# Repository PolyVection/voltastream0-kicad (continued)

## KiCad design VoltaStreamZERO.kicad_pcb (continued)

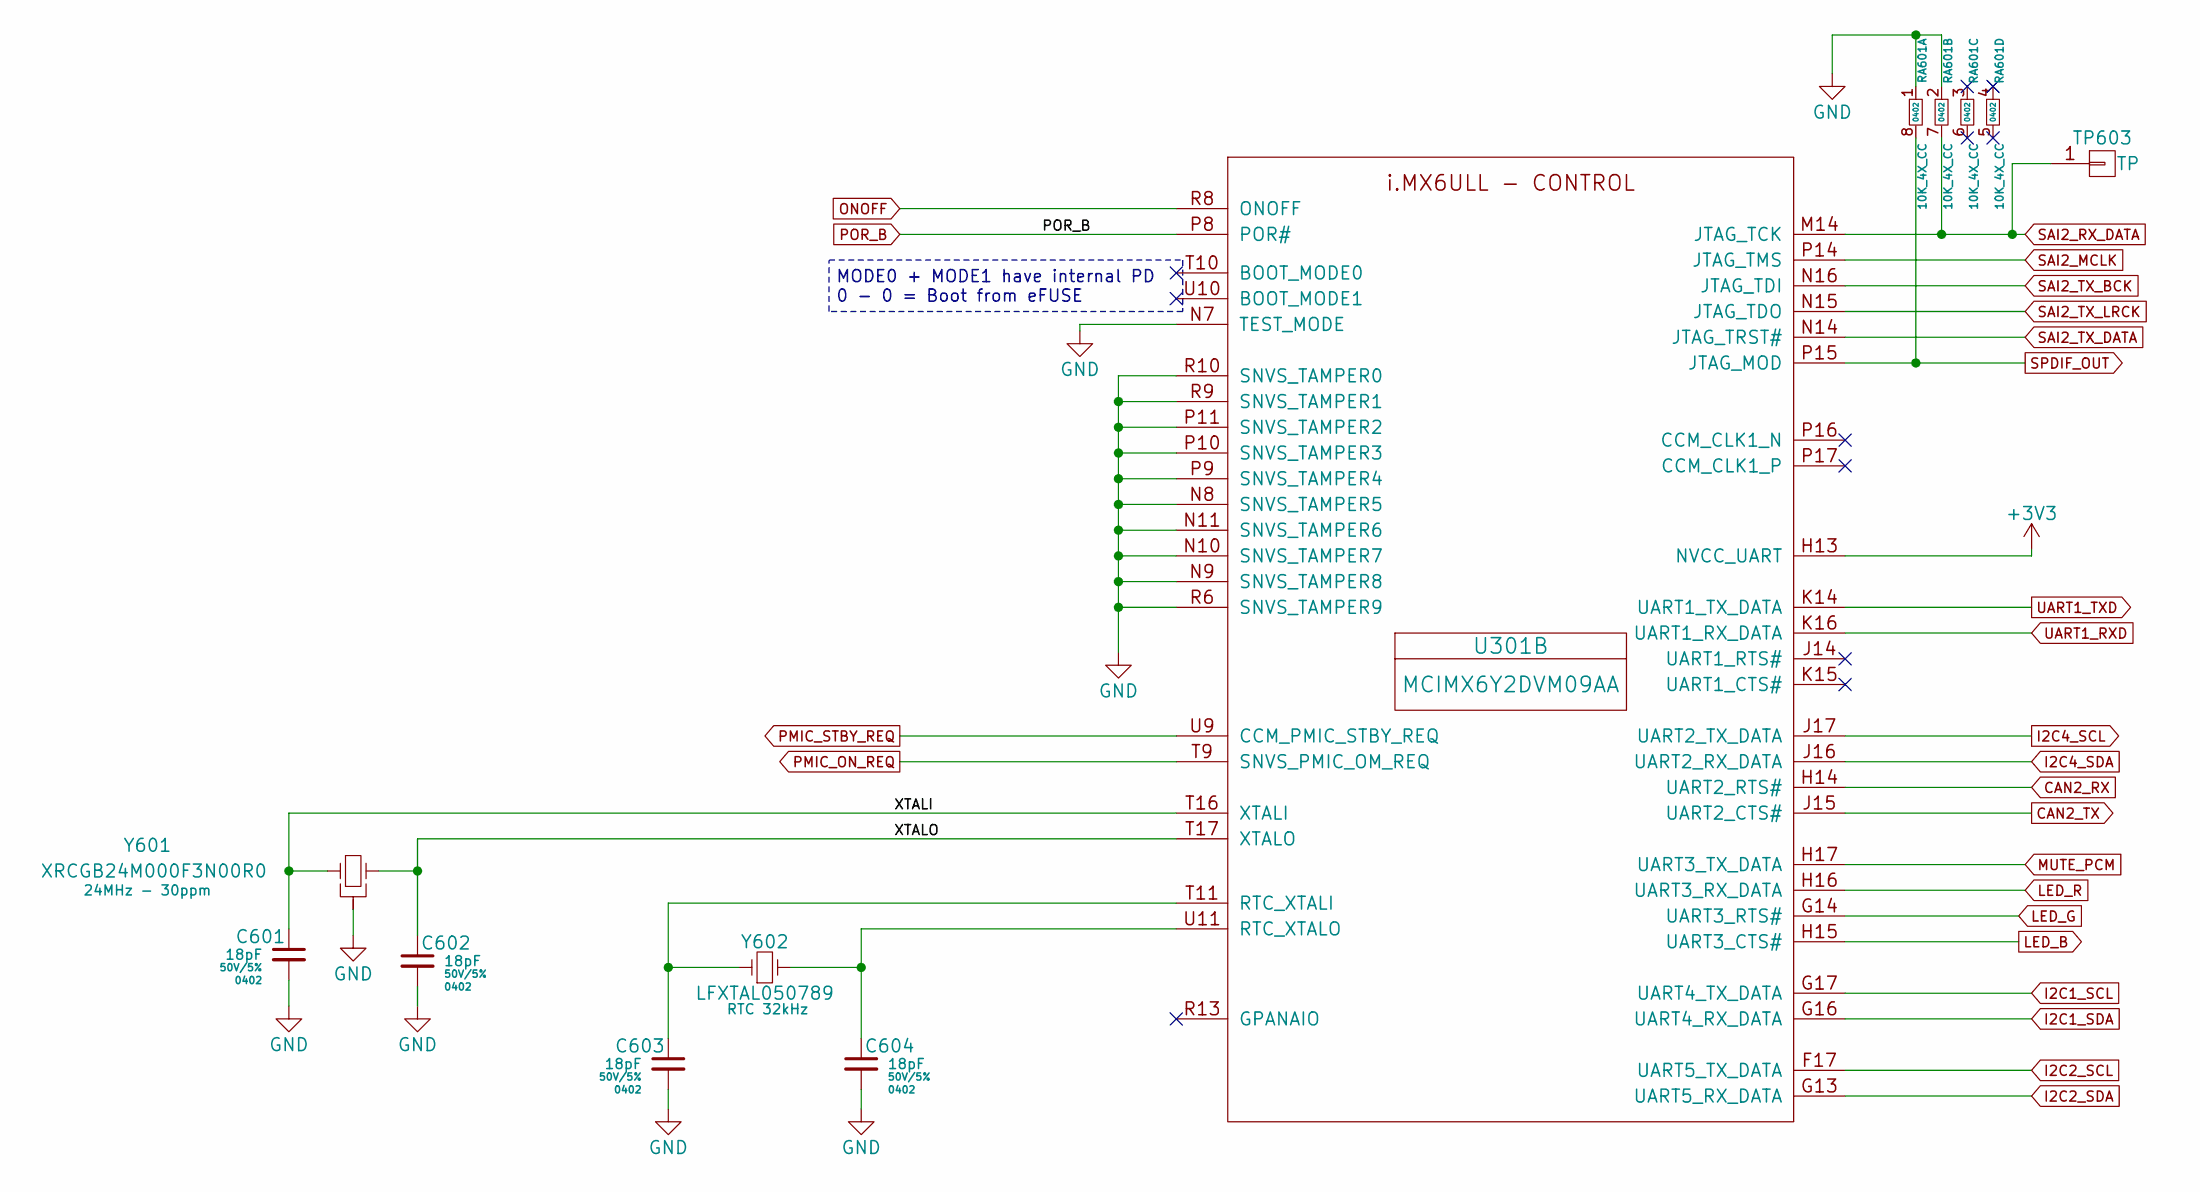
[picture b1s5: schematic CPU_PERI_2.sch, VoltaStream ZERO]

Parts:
C601, C602, C603, C604: 18pF; 0402; Rating 50V/5%; Rating2 C0G; Part GRM1555C1H180JA01D
RA601: 10K_4X_CC; R_Array_OPT_4x0402; Rating 10K, 5%; Rating2 Concave Array 4x; Part EXB-N8V103JX
TP603: TP; TP_10; Rating NoMask; Part TestPoint
U301: MCIMX6Y2DVM09AA; BGA_14x14; Rating 1x 900 MHz, 32 bit; Part MCIMX6Y2DVM09AA
Y601: XRCGB24M000F3N00R0; OSZ_2x1.6; Rating 24MHz - 30ppm; Rating2 6pF - 2x1.6mm; Part XRCGB24M000F3N00R0
Y602: LFXTAL050789; OSZ_2x1.2; Rating RTC 32kHz; Part LFXTAL050789Reel

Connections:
+3V3: U301.H13 (NVCC_UART); also elsewhere on the board
/CPU_PERI_2/XTALI: C601.1, U301.T16 (XTALI), Y601.1
/CPU_PERI_2/XTALO: C602.1, U301.T17 (XTALO), Y601.2
CAN2_RX: U301.H14 (UART2_RTS#)
CAN2_TX: U301.J15 (UART2_CTS#)
GND: C601.2, C602.2, C603.2, C604.2, RA601.1, RA601.2 (P1), U301.N7 (TEST_MODE), U301.N8 (SNVS_TAMPER5), U301.N9 (SNVS_TAMPER8), U301.N10 (SNVS_TAMPER7), U301.N11 (SNVS_TAMPER6), U301.P9 (SNVS_TAMPER4), U301.P10 (SNVS_TAMPER3), U301.P11 (SNVS_TAMPER2), U301.R6 (SNVS_TAMPER9), U301.R9 (SNVS_TAMPER1), U301.R10 (SNVS_TAMPER0), Y601.G; also elsewhere on the board
I2C1_SCL: U301.G17 (UART4_TX_DATA); also elsewhere on the board
I2C1_SDA: U301.G16 (UART4_RX_DATA); also elsewhere on the board
I2C2_SCL: U301.F17 (UART5_TX_DATA)
I2C2_SDA: U301.G13 (UART5_RX_DATA)
I2C4_SCL: U301.J17 (UART2_TX_DATA); also elsewhere on the board
I2C4_SDA: U301.J16 (UART2_RX_DATA); also elsewhere on the board
LED_B: U301.H15 (UART3_CTS#); also elsewhere on the board
LED_G: U301.G14 (UART3_RTS#); also elsewhere on the board
LED_R: U301.H16 (UART3_RX_DATA); also elsewhere on the board
MUTE_PCM: U301.H17 (UART3_TX_DATA); also elsewhere on the board
unnamed: C603.1, U301.T11 (RTC_XTALI), Y602.1
unnamed: C604.1, U301.U11 (RTC_XTALO), Y602.2
ONOFF: U301.R8 (ONOFF); also elsewhere on the board
PMIC_ON_REQ: U301.T9 (SNVS_PMIC_OM_REQ); also elsewhere on the board
PMIC_STBY_REQ: U301.U9 (CCM_PMIC_STBY_REQ)
POR_B: U301.P8 (POR#); also elsewhere on the board
SAI2_MCLK: U301.P14 (JTAG_TMS); also elsewhere on the board
SAI2_RX_DATA: RA601.7 (R1), TP603.1, U301.M14 (JTAG_TCK)
SAI2_TX_BCK: U301.N16 (JTAG_TDI); also elsewhere on the board
SAI2_TX_DATA: U301.N14 (JTAG_TRST#); also elsewhere on the board
SAI2_TX_LRCK: U301.N15 (JTAG_TDO); also elsewhere on the board
SPDIF_OUT: RA601.8 (R1), U301.P15 (JTAG_MOD); also elsewhere on the board
UART1_RXD: U301.K16 (UART1_RX_DATA); also elsewhere on the board
UART1_TXD: U301.K14 (UART1_TX_DATA); also elsewhere on the board

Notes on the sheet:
MODE0 + MODE1 have internal PD 0 - 0 = Boot from eFUSE

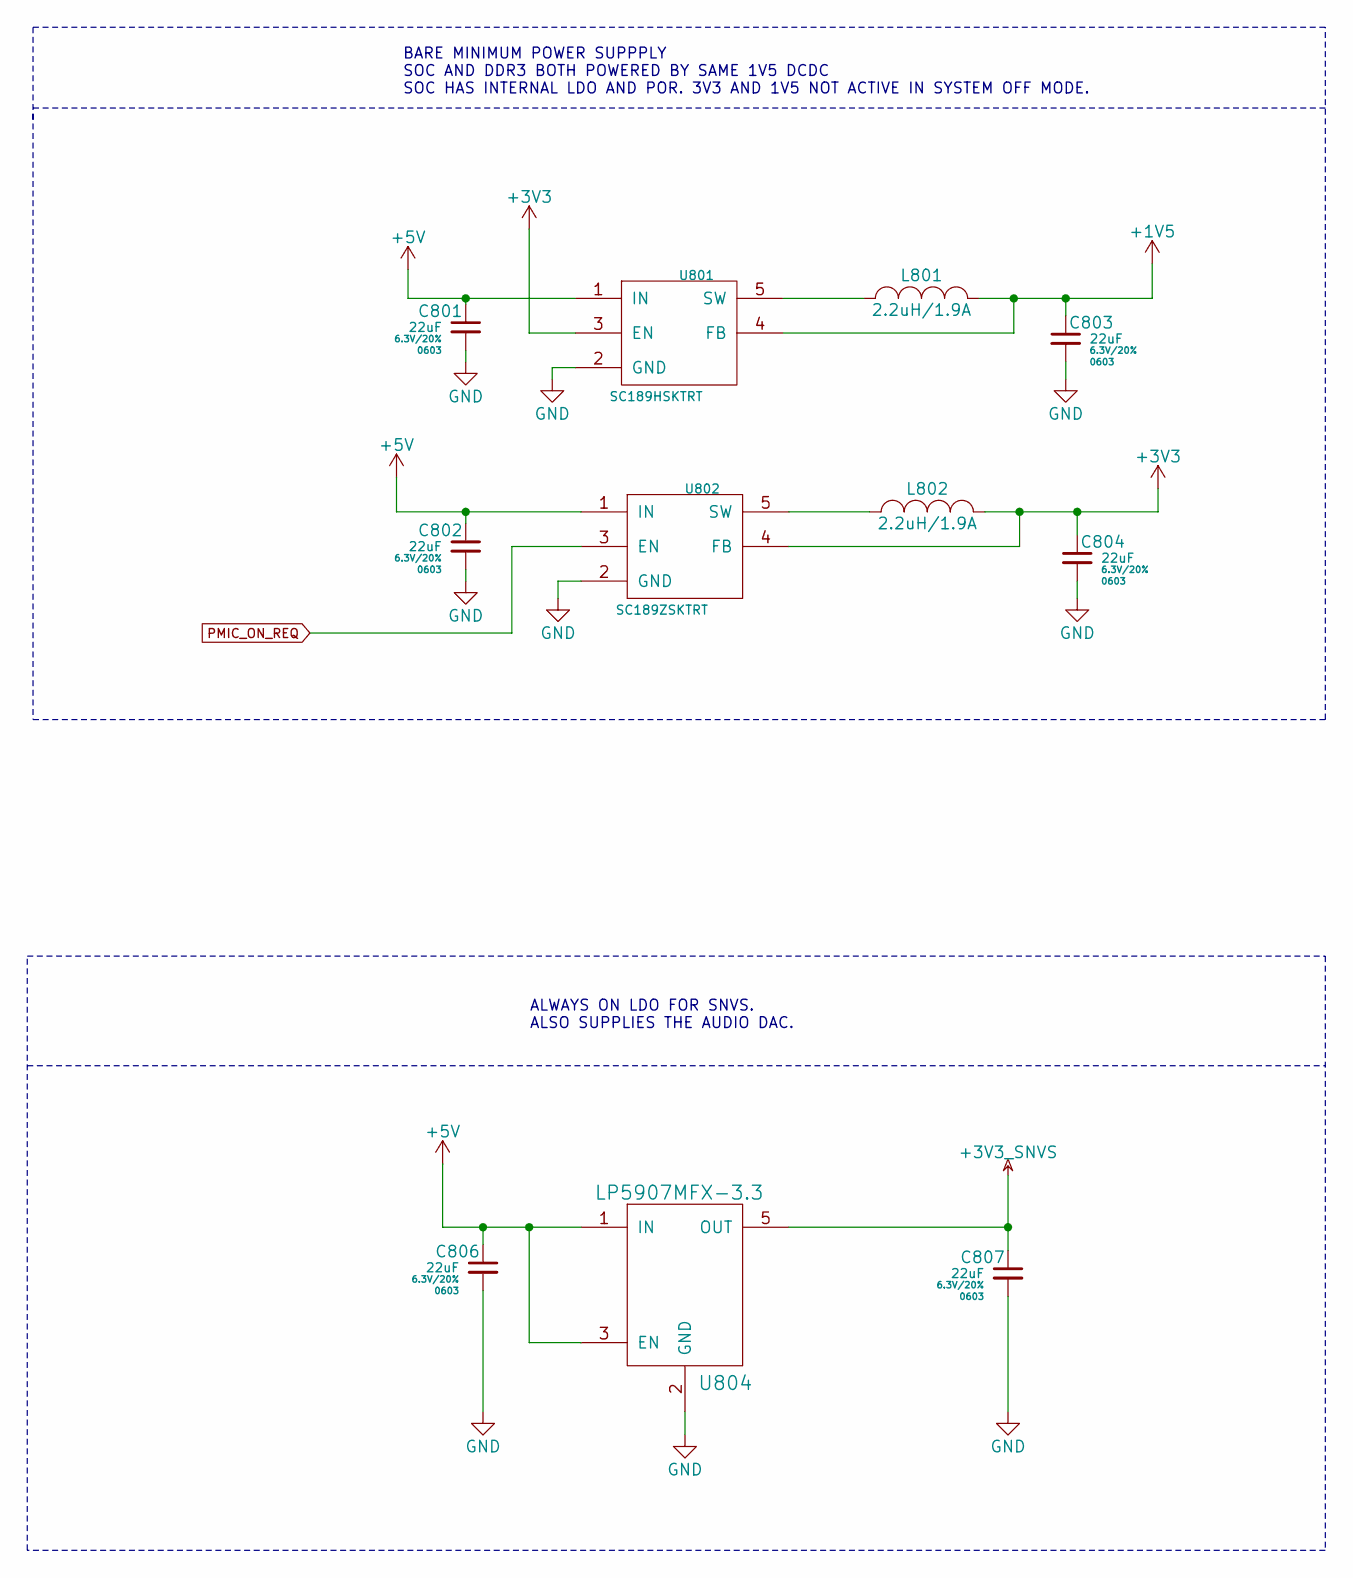
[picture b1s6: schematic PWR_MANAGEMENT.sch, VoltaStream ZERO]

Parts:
C801, C802, C803, C804, C806, C807: 22uF; 0603; Rating 6.3V/20%; Rating2 X5R; Part GRM188R60J226ME0D
L801, L802: 2.2uH/1.9A; MAMK2520T2R2M; Rating 2.2uH / 1.9A; Part MAMK2520T2R2M
U801: SC189HSKTRT; SOT-23-5; Rating 1V5 1.5A 2.5MHz; Rating2 STEP DOWN; Part SC189HSKTRT
U802: SC189ZSKTRT; SOT-23-5; Rating 3V3 1.5A 2.5MHz; Rating2 STEP DOWN; Part SC189ZSKTRT
U804: LP5907MFX-3.3; SOT-23-5; Rating 3V3 LDO LOW-NOISE; Rating2 250mA; Part LP5907MFX-3.3

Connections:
+1V5: C803.1, L801.2, U801.4 (FB); also elsewhere on the board
+3V3: C804.1, L802.2, U801.3 (EN), U802.4 (FB); also elsewhere on the board
+3V3_SNVS: C807.1, U804.5 (OUT); also elsewhere on the board
+5V: C801.1, C802.1, C806.1, U801.1 (IN), U802.1 (IN), U804.1 (IN), U804.3 (EN); also elsewhere on the board
GND: C801.2, C802.2, C803.2, C804.2, C806.2, C807.2, U801.2 (GND), U802.2 (GND), U804.2 (GND); also elsewhere on the board
unnamed: L801.1, U801.5 (SW)
unnamed: L802.1, U802.5 (SW)
PMIC_ON_REQ: U802.3 (EN); also elsewhere on the board

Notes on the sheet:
BARE MINIMUM POWER SUPPPLY SOC AND DDR3 BOTH POWERED BY SAME 1V5 DCDC SOC HAS INTERNAL LDO AND POR. 3V3 AND 1V5 NOT ACTIVE IN SYSTEM OFF MODE.
ALWAYS ON LDO FOR SNVS. ALSO SUPPLIES THE AUDIO DAC.

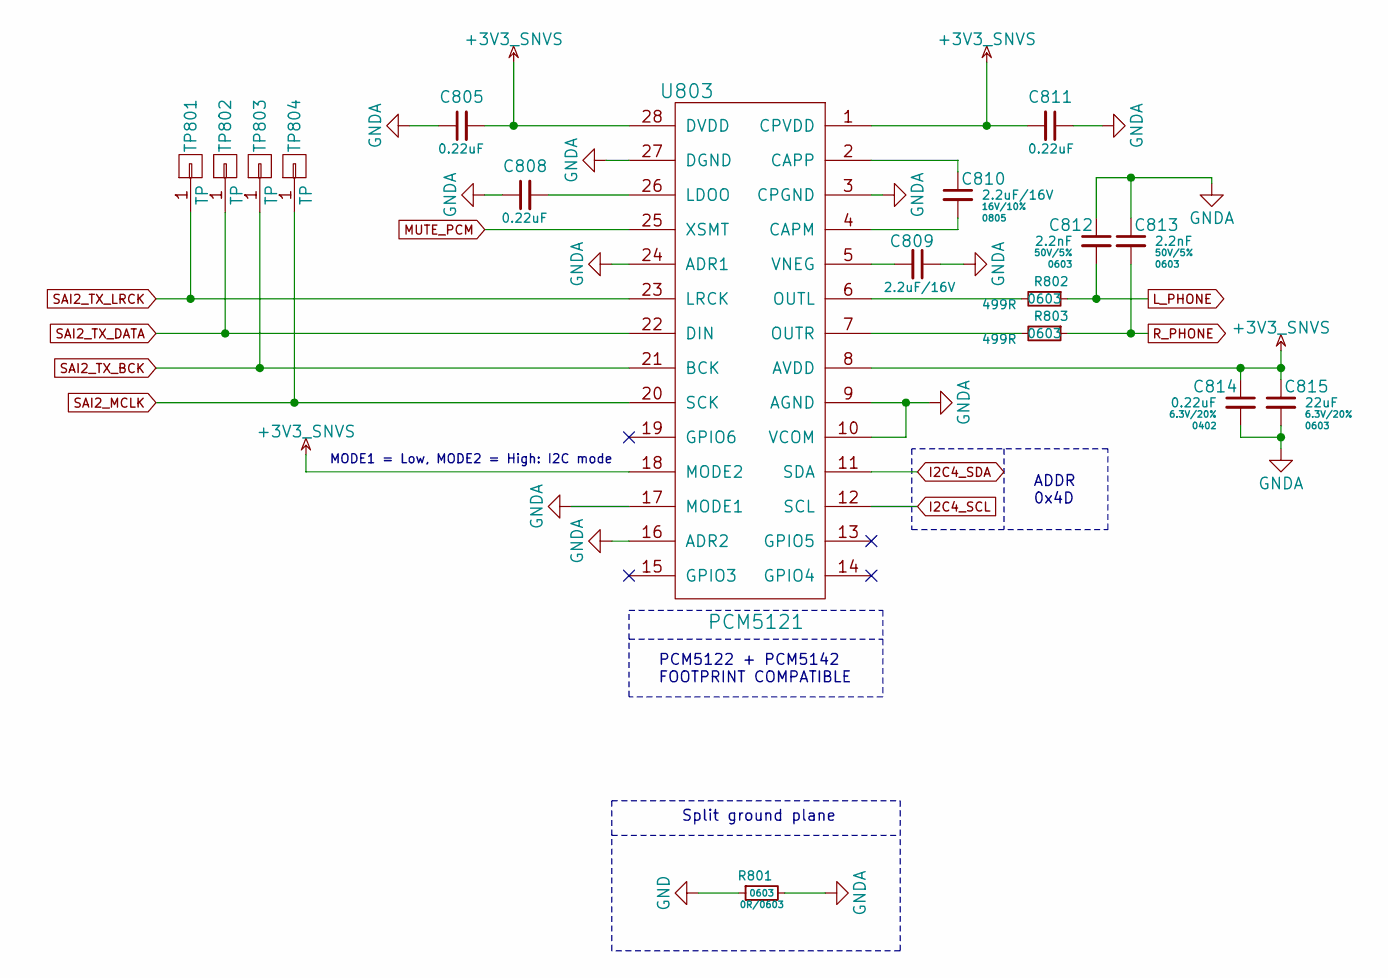
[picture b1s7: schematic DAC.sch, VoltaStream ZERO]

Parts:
C805, C808, C811, C814: 0.22uF; 0402; Rating 6.3V/20%; Rating2 X5R; Part GRM155R60J224KE01D
C809, C810: 2.2uF/16V; 0805; Rating 16V/10%; Rating2 X7R; Part GRM21BR71C225KA12L
C812, C813: 2.2nF; 0603; Rating 50V/5%; Rating2 X7R; Part GRM188R71H222JA01D
C815: 22uF; 0603; Rating 6.3V/20%; Rating2 X5R; Part GRM188R60J226ME0D
R801: 0R/0603; 0603; Rating 1% / Thick Film; Part RC0603FR-070RL
R802, R803: 499R; 0603; Rating 1% / Thick Film; Part RC0603FR-07499RL
TP801, TP802, TP803, TP804: TP; TP_10; Rating NoMask; Part TestPoint
U803: PCM5121; TSSOP-28_4.4x9.7mm_Pitch0.65mm; Rating 106dB DAC BurrBrown; Rating2 HW VOLUME; Part PCM5121PWR

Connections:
+3V3_SNVS: C805.2, C811.2, C814.1, C815.1, U803.1 (CPVDD), U803.8 (AVDD), U803.18 (MODE2), U803.28 (DVDD); also elsewhere on the board
GND: R801.1; also elsewhere on the board
GNDA: C805.1, C808.1, C809.1, C811.1, C812.1, C813.1, C814.2, C815.2, R801.2, U803.3 (CPGND), U803.9 (AGND), U803.10 (VCOM), U803.16 (ADR2), U803.17 (MODE1), U803.24 (ADR1), U803.27 (DGND); also elsewhere on the board
I2C4_SCL: U803.12 (SCL); also elsewhere on the board
I2C4_SDA: U803.11 (SDA); also elsewhere on the board
L_PHONE: C812.2, R802.1; also elsewhere on the board
MUTE_PCM: U803.25 (XSMT); also elsewhere on the board
unnamed: C808.2, U803.26 (LDOO)
unnamed: C809.2, U803.5 (VNEG)
unnamed: C810.1, U803.2 (CAPP)
unnamed: C810.2, U803.4 (CAPM)
unnamed: R802.2, U803.6 (OUTL)
unnamed: R803.2, U803.7 (OUTR)
R_PHONE: C813.2, R803.1; also elsewhere on the board
SAI2_MCLK: TP804.1, U803.20 (SCK); also elsewhere on the board
SAI2_TX_BCK: TP803.1, U803.21 (BCK); also elsewhere on the board
SAI2_TX_DATA: TP802.1, U803.22 (DIN); also elsewhere on the board
SAI2_TX_LRCK: TP801.1, U803.23 (LRCK); also elsewhere on the board

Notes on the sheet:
MODE1 = Low, MODE2 = High: I2C mode
Split ground plane
ADDR 0x4D
PCM5122 + PCM5142 FOOTPRINT COMPATIBLE

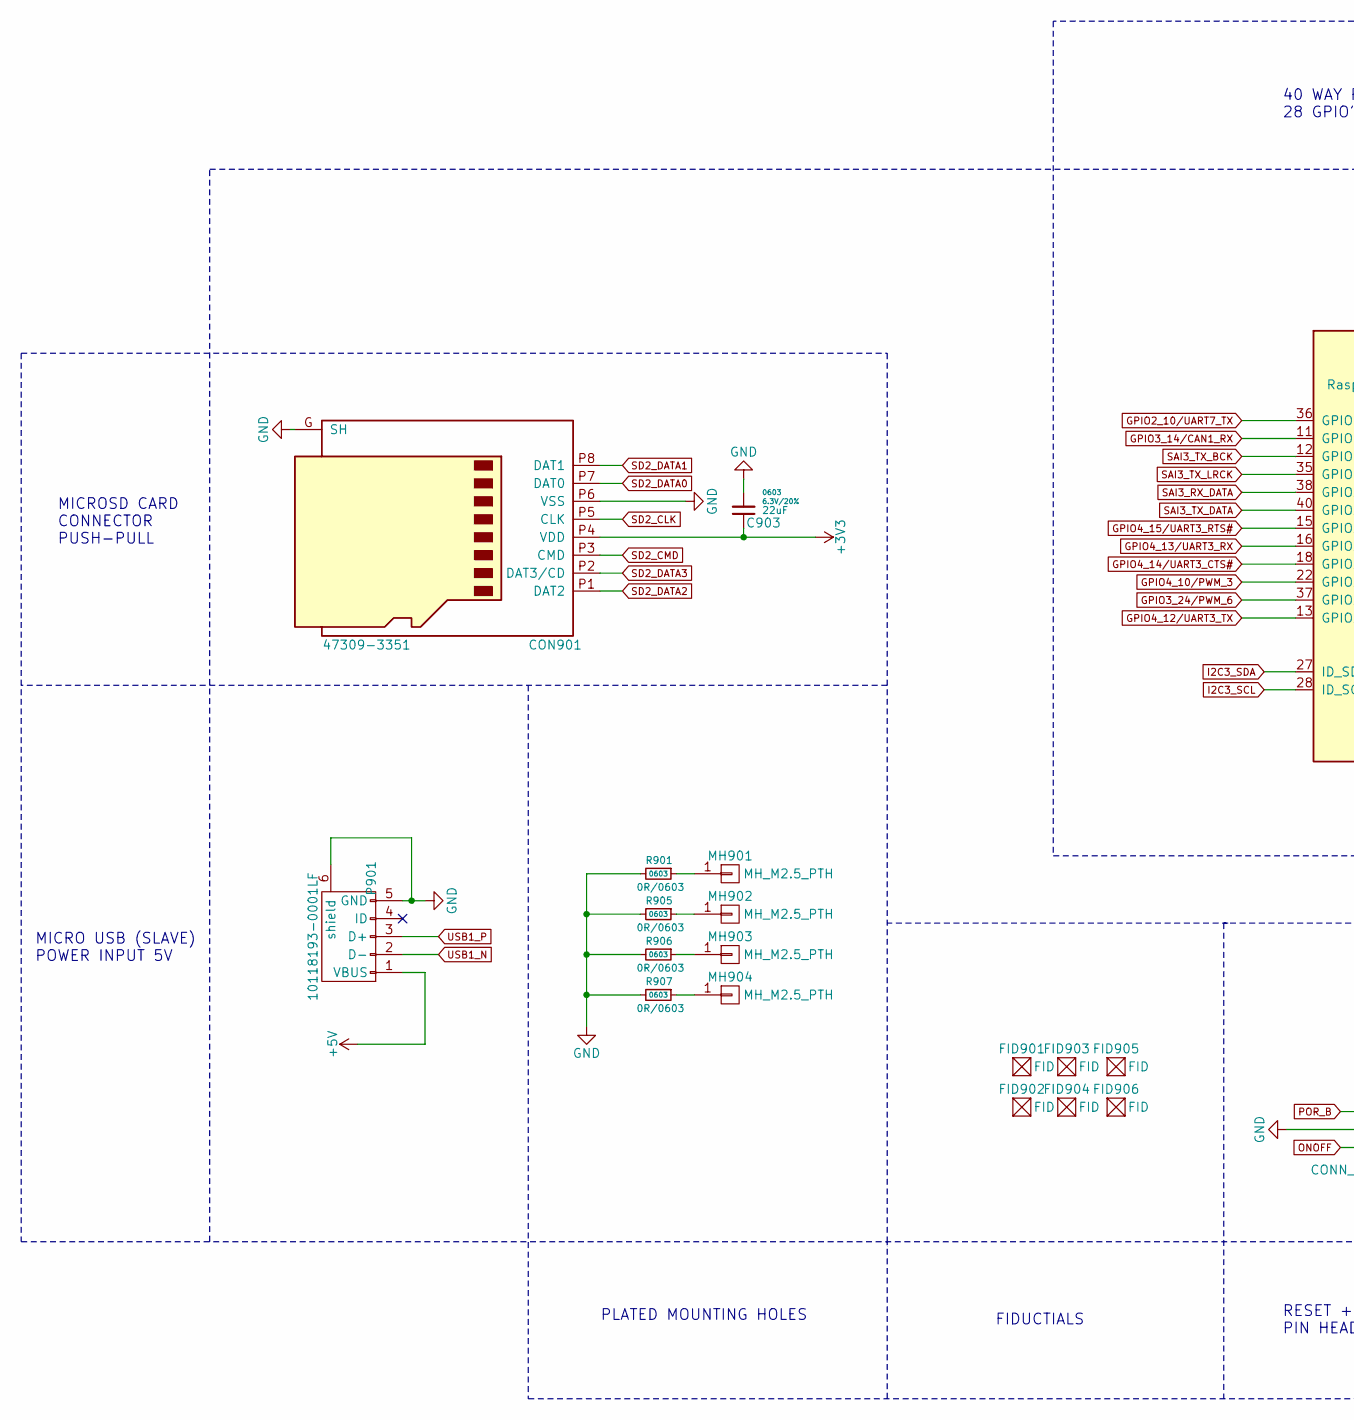
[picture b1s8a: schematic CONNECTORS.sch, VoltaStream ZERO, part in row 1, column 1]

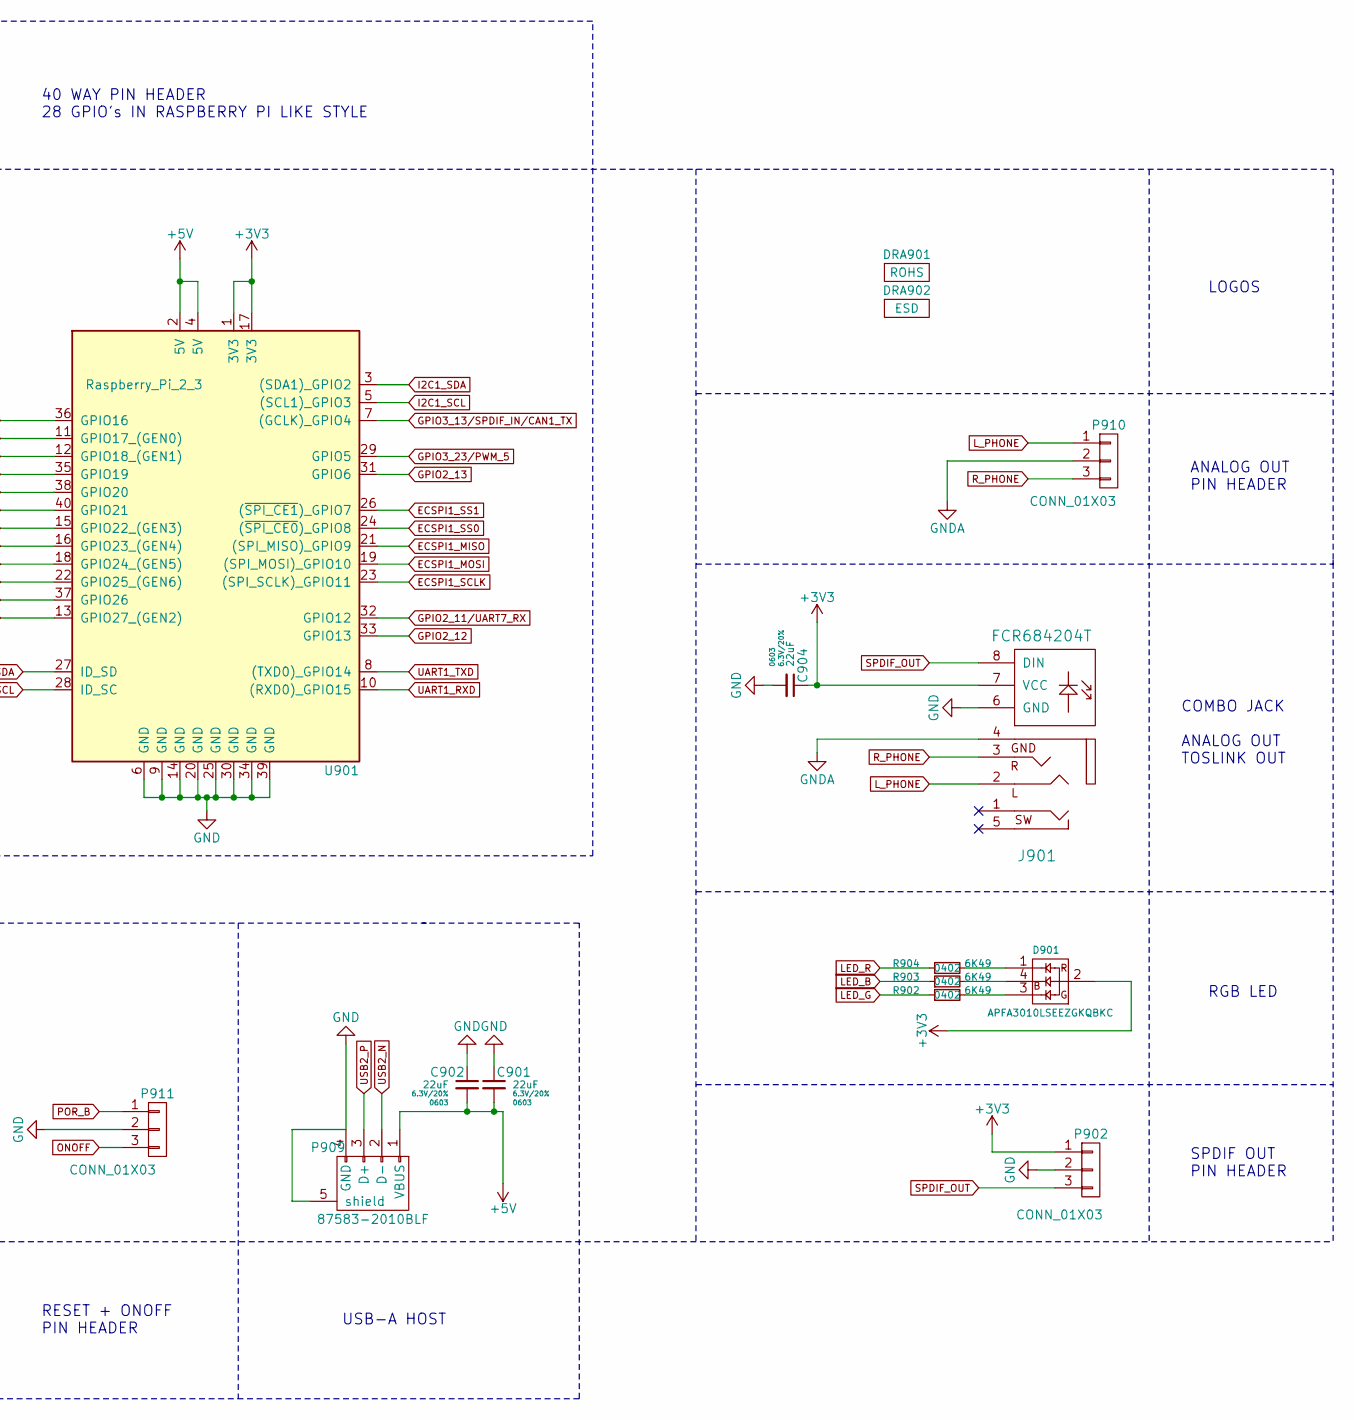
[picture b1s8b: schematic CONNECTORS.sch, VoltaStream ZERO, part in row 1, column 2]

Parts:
C901, C902, C903, C904: 22uF; 0603; Rating 6.3V/20%; Rating2 X5R; Part GRM188R60J226ME0D
CON901: 47309-3351; Rating MicroSD connector; Rating2 Push-Pull SHORT 2MM; Part 47309-3351
D901: APFA3010LSEEZGKQBKC; Rating RGB 90 DEG; Rating2 2mA; Part APFA3010LSEEZGKQ
DRA901: ROHS; Logo_silk_ROHS_5x2.8mm
DRA902: ESD; ESD-Logo_6.6x6mm_SilkScreen
FID901, FID902, FID903, FID904, FID905, FID906: FID; Fiducial_1mm; Rating NoMask; Part Fiductial
J901: FCR684204T; Rating 3.5mm HP + TOSLINK; Part FCR684204T
MH901, MH902, MH903, MH904: MH_M2.5_PTH; MountingHole_2.7mm_M2.5_Pad_Via; Rating Mounting Hole M2.5 VIA; Rating2 PTH
P901: 10118193-0001LF; Rating microUSB OTG; Part 10118193-0001LF
P902, P910, P911: CONN_01X03; Pin_Header_Straight_1x03
P909: 87583-2010BLF; Rating USB-A SINGLE SMD; Part 87583-2010BLF
R901, R905, R906, R907: 0R/0603; 0603; Rating 1% / Thick Film; Part RC0603FR-070RL
R902, R903, R904: 6K49; 0402; Rating 1% / Thick Film; Part RC0402FR-076K49L
U901: Raspberry_Pi_2_3; Pin_Header_Straight_2x20

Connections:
+3V3: C903.1, C904.1, CON901.P4 (VDD), D901.2, J901.7 (VCC), P902.1, U901.1 (3V3), U901.17 (3V3); also elsewhere on the board
+5V: C901.2, C902.2, P901.1 (VBUS), P909.1 (VBUS), U901.2 (5V), U901.4 (5V); also elsewhere on the board
ECSPI1_MISO: U901.21 ((SPI_MISO)_GPIO9); also elsewhere on the board
ECSPI1_MOSI: U901.19 ((SPI_MOSI)_GPIO10); also elsewhere on the board
ECSPI1_SCLK: U901.23 ((SPI_SCLK)_GPIO11); also elsewhere on the board
ECSPI1_SS0: U901.24 ((~SPI_CE0~)_GPIO8); also elsewhere on the board
ECSPI1_SS1: U901.26 ((~SPI_CE1~)_GPIO7); also elsewhere on the board
GND: C901.1, C902.1, C903.2, C904.2, CON901.G (SH), CON901.P6 (VSS), J901.6 (GND), P901.5 (GND), P901.6 (shield), P902.2, P909.4 (GND), P909.5 (shield), P911.2, R901.2, R905.2, R906.2, R907.2, U901.6 (GND), U901.9 (GND), U901.14 (GND), U901.20 (GND), U901.25 (GND), U901.30 (GND), U901.34 (GND), U901.39 (GND); also elsewhere on the board
GNDA: J901.4, P910.2; also elsewhere on the board
GPIO2_10/UART7_TX: U901.36 (GPIO16); also elsewhere on the board
GPIO2_11/UART7_RX: U901.32 (GPIO12); also elsewhere on the board
GPIO2_12: U901.33 (GPIO13); also elsewhere on the board
GPIO2_13: U901.31 (GPIO6); also elsewhere on the board
GPIO3_13/SPDIF_IN/CAN1_TX: U901.7 ((GCLK)_GPIO4); also elsewhere on the board
GPIO3_14/CAN1_RX: U901.11 (GPIO17_(GEN0)); also elsewhere on the board
GPIO3_23/PWM_5: U901.29 (GPIO5); also elsewhere on the board
GPIO3_24/PWM_6: U901.37 (GPIO26); also elsewhere on the board
GPIO4_10/PWM_3: U901.22 (GPIO25_(GEN6)); also elsewhere on the board
GPIO4_12/UART3_TX: U901.13 (GPIO27_(GEN2)); also elsewhere on the board
GPIO4_13/UART3_RX: U901.16 (GPIO23_(GEN4)); also elsewhere on the board
GPIO4_14/UART3_CTS#: U901.18 (GPIO24_(GEN5)); also elsewhere on the board
GPIO4_15/UART3_RTS#: U901.15 (GPIO22_(GEN3)); also elsewhere on the board
I2C1_SCL: U901.5 ((SCL1)_GPIO3); also elsewhere on the board
I2C1_SDA: U901.3 ((SDA1)_GPIO2); also elsewhere on the board
I2C3_SCL: U901.28 (ID_SC); also elsewhere on the board
I2C3_SDA: U901.27 (ID_SD); also elsewhere on the board
LED_B: R903.1; also elsewhere on the board
LED_G: R902.1; also elsewhere on the board
LED_R: R904.1; also elsewhere on the board
L_PHONE: J901.2, P910.1; also elsewhere on the board
unnamed: D901.1, R904.2
unnamed: D901.3, R902.2
unnamed: D901.4, R903.2
unnamed: MH901.1, R901.1
unnamed: MH902.1, R905.1
unnamed: MH903.1, R906.1
unnamed: MH904.1, R907.1
ONOFF: P911.3; also elsewhere on the board
POR_B: P911.1; also elsewhere on the board
R_PHONE: J901.3, P910.3; also elsewhere on the board
SAI3_RX_DATA: U901.38 (GPIO20); also elsewhere on the board
SAI3_TX_BCK: U901.12 (GPIO18_(GEN1)); also elsewhere on the board
SAI3_TX_DATA: U901.40 (GPIO21); also elsewhere on the board
SAI3_TX_LRCK: U901.35 (GPIO19); also elsewhere on the board
SD2_CLK: CON901.P5 (CLK); also elsewhere on the board
SD2_CMD: CON901.P3 (CMD); also elsewhere on the board
SD2_DATA0: CON901.P7 (DAT0); also elsewhere on the board
SD2_DATA1: CON901.P8 (DAT1); also elsewhere on the board
SD2_DATA2: CON901.P1 (DAT2); also elsewhere on the board
SD2_DATA3: CON901.P2 (DAT3/CD); also elsewhere on the board
SPDIF_OUT: J901.8 (DIN), P902.3; also elsewhere on the board
UART1_RXD: U901.10 ((RXD0)_GPIO15); also elsewhere on the board
UART1_TXD: U901.8 ((TXD0)_GPIO14); also elsewhere on the board
USB1_N: P901.2 (D-); also elsewhere on the board
USB1_P: P901.3 (D+); also elsewhere on the board
USB2_N: P909.2 (D-); also elsewhere on the board
USB2_P: P909.3 (D+); also elsewhere on the board

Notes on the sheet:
SPDIF OUT PIN HEADER
RGB LED
COMBO JACK ANALOG OUT TOSLINK OUT
ANALOG OUT PIN HEADER
MICROSD CARD CONNECTOR PUSH-PULL
MICRO USB (SLAVE) POWER INPUT 5V
PLATED MOUNTING HOLES
RESET + ONOFF PIN HEADER
USB-A HOST
40 WAY PIN HEADER 28 GPIO's IN RASPBERRY PI LIKE STYLE
LOGOS
FIDUCTIALS

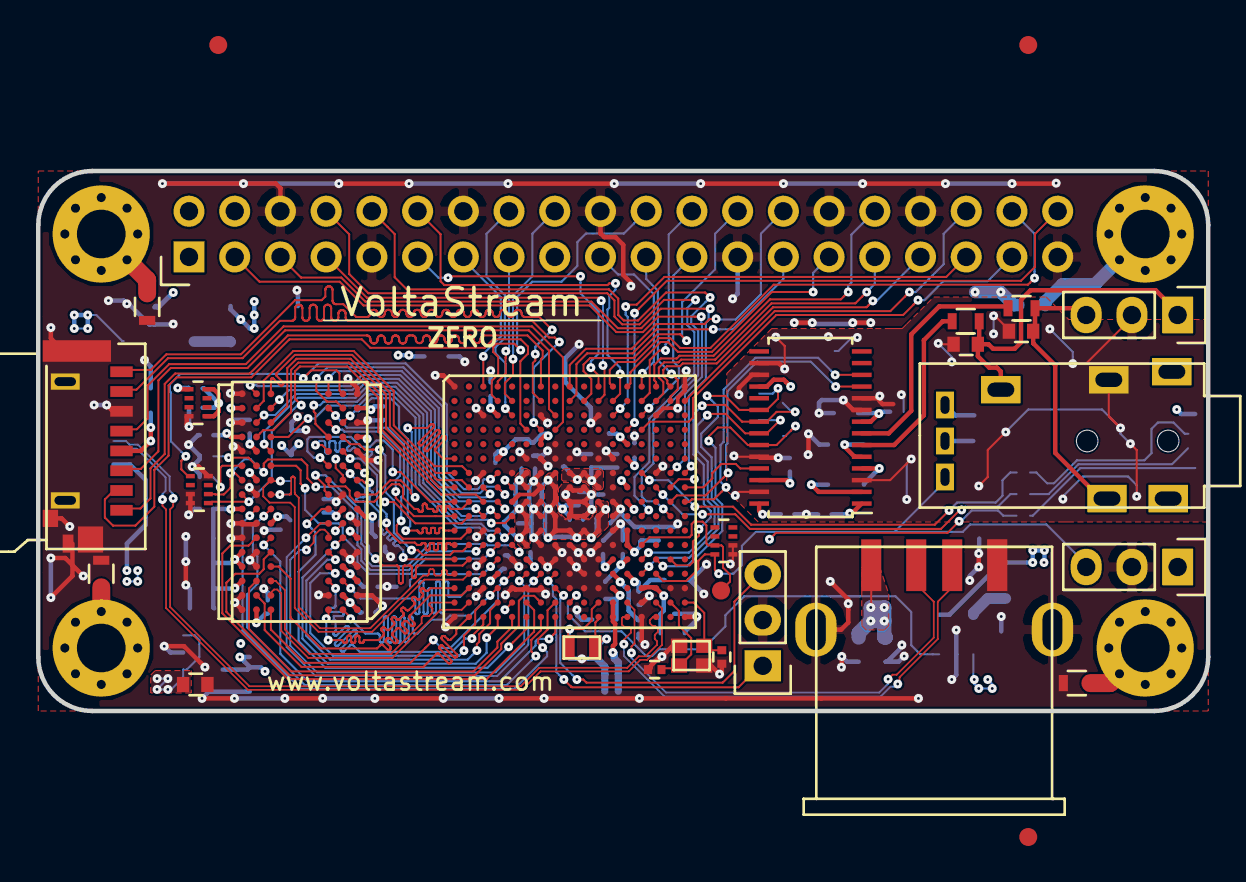
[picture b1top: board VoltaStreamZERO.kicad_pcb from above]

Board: 4 copper layers, 65.0 x 30.0 mm, 128 parts (0 on the bottom side), 143 nets.

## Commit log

2017-08-08 Rev. A1
